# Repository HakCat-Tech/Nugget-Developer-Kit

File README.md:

# WiFi Nugget Developer Kit v3.0.x
This repository contains KiCAD design files for the WiFi Nugget Developer Kit PCB.  The current version of this release is `3.0.1`.
This kit is designed to teach beginners basic hardware assembly skills, and features both through-hole and surface mount components.
<p align="center">
  <br>
  
  <br>
  <b>ESP32-S2 DevKit Components</b>
  <br>
  <br>
</p>

## Features
This kit is designed to work with the [Wemos "mini" form factor](https://www.wemos.cc/en/latest/), and accomodates breakouts for the ESP8266, ESP32-S2, and some other Espressif based board designs.
The developer kit includes:

- **Buttons** (D-Pad style, 4 Buttons)
- **RGB LED** (WS2812B NeoPixel)
- **WiFi Microcontroller** ([D1](https://www.wemos.cc/en/latest/d1/index.html)/[S2](https://www.wemos.cc/en/latest/s2/index.html)/[C3](https://www.wemos.cc/en/latest/c3/index.html) Mini)
- **Screen** (SH1106 1.3" OLED)
- **Expansion Headers** 
- **Screw Assembly*** (M2.5 Screws / Threaded Inserts)
- **3D Printed Case***

\* *We ditched the screw assembly on newer Nuggets, which use a snap-fit case.  You can find links to our case designs below.*

## Resources
- [Assembly Guide]()
- [3D printed cases](https://github.com/HakCat-Tech/WiFi-Nugget-Cases)

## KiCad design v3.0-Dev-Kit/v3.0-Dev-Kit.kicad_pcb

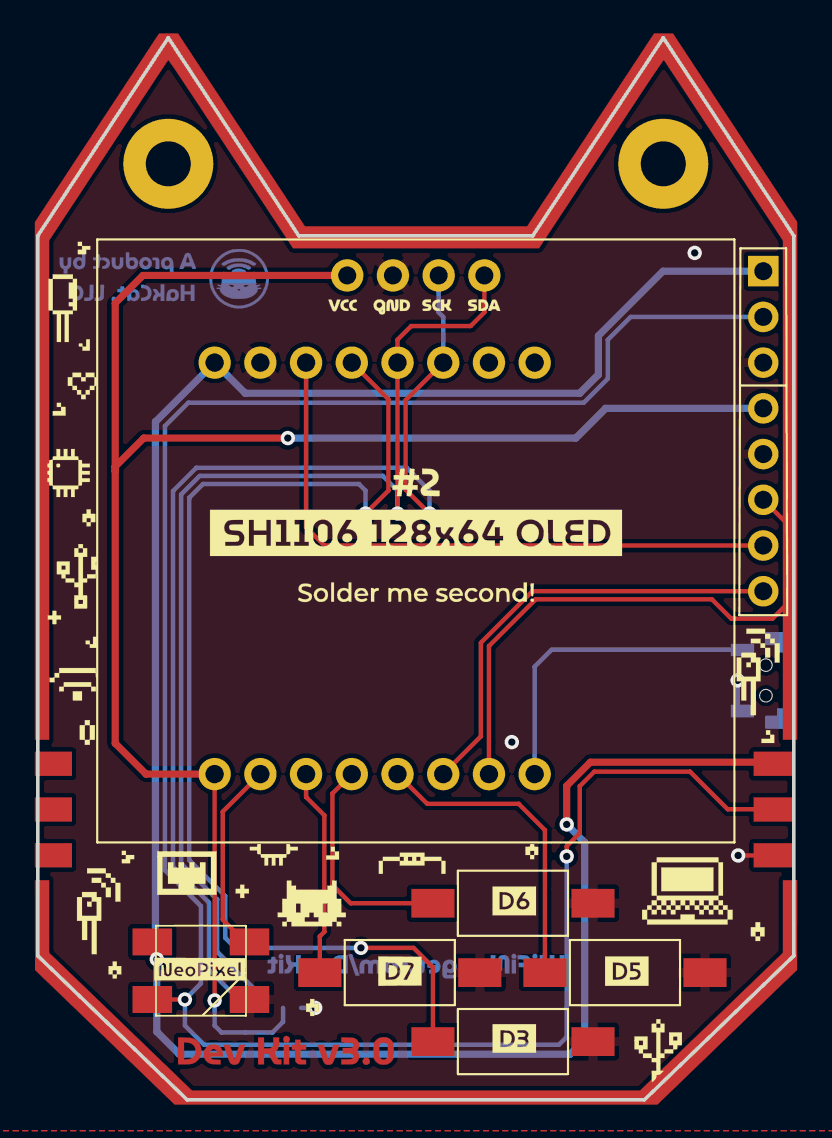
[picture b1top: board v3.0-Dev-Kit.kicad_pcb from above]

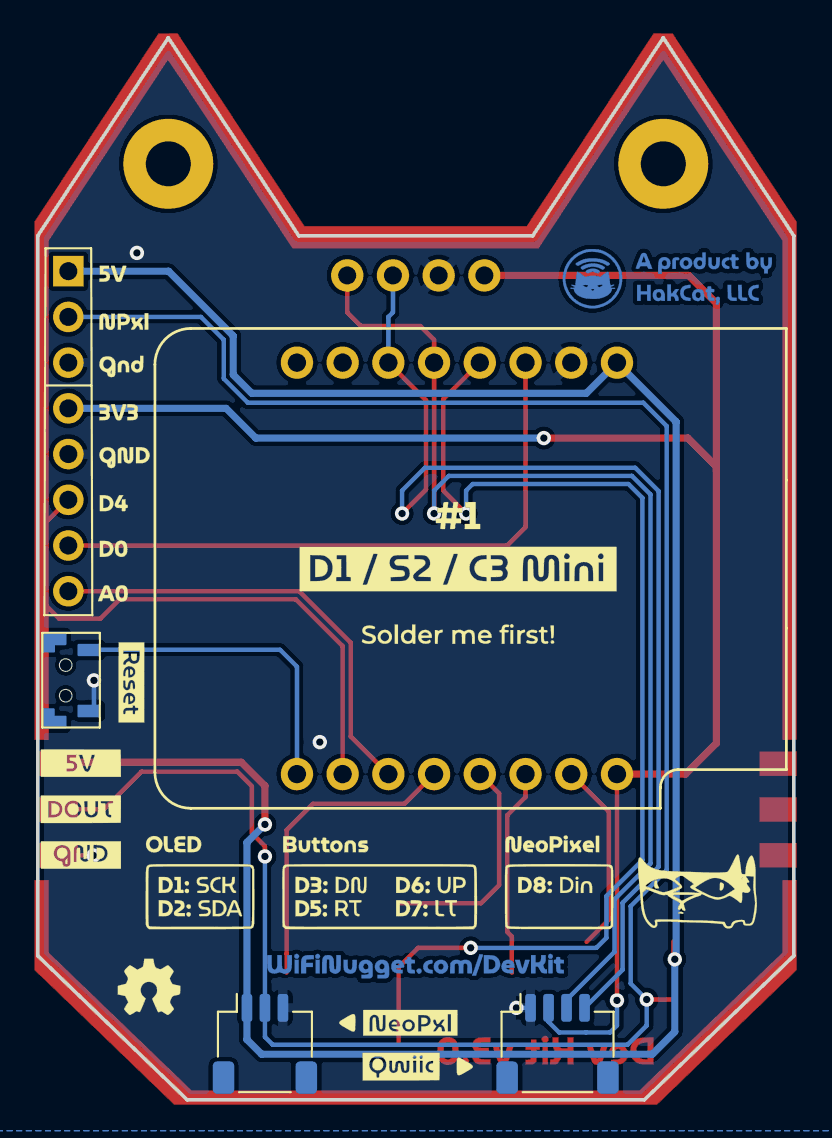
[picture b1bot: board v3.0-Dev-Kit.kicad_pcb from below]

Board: 2 copper layers, 42.0 x 59.0 mm, 10 parts (2 on the bottom side), 15 nets.

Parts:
Brd1: SH1106 OLED; SH1106-128x64-OLED
D1: WS2812B; LED_WS2812B_PLCC4_5.0x5.0mm_P3.2mm_idiot_proof
J1: 8 Pin Header; PinHeader_1x08_P2.54mm_Vertical
Ref**: Val**; v3.0
SW1: Up; SW_SPST_FSMSM
SW2: Down; SW_SPST_FSMSM
SW3: Left; SW_SPST_FSMSM
SW4: Right; SW_SPST_FSMSM
SW5: botton
U1: WeMos D1 Mini; wemos-d1-mini-with-pin-header-and-connector

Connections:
+5V: D1.1, J1.1, U1.9
/D5: SW4.1, U1.4
/D6: SW1.1, U1.5
/D7: SW3.1, U1.6
GND: Brd1.2, D1.3, J1.3, J1.5, SW1.2, SW2.2, SW3.2, SW4.2, SW5.2, U1.10
unnamed: Brd1.1, J1.4, U1.8
unnamed: Brd1.3, U1.14
unnamed: Brd1.4, U1.13
unnamed: D1.2, J1.2
unnamed: D1.4, U1.7
unnamed: SW5.3, U1.1
unnamed: J1.8, U1.3
unnamed: J1.7, U1.11
unnamed: J1.6, U1.2
unnamed: SW2.1, U1.12

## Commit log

2022-05-15 publish v2.0 PCB design files & art assets
2022-05-15 upload v2.1 files
2022-05-18 update v2.2 - delete old graphics
2022-05-18 Update version number
2022-05-18 push alpha v3.0 PCB
2022-05-19 update colliding trace
2022-05-19 export BOM and positioning files
2022-05-19 add export files
2022-06-14 update v3.0.1 - added JST PH connector for NeoPixel breakout, fixed bridging solder design flaw
2022-06-30 Update v3.0.1 graphics & board outline
